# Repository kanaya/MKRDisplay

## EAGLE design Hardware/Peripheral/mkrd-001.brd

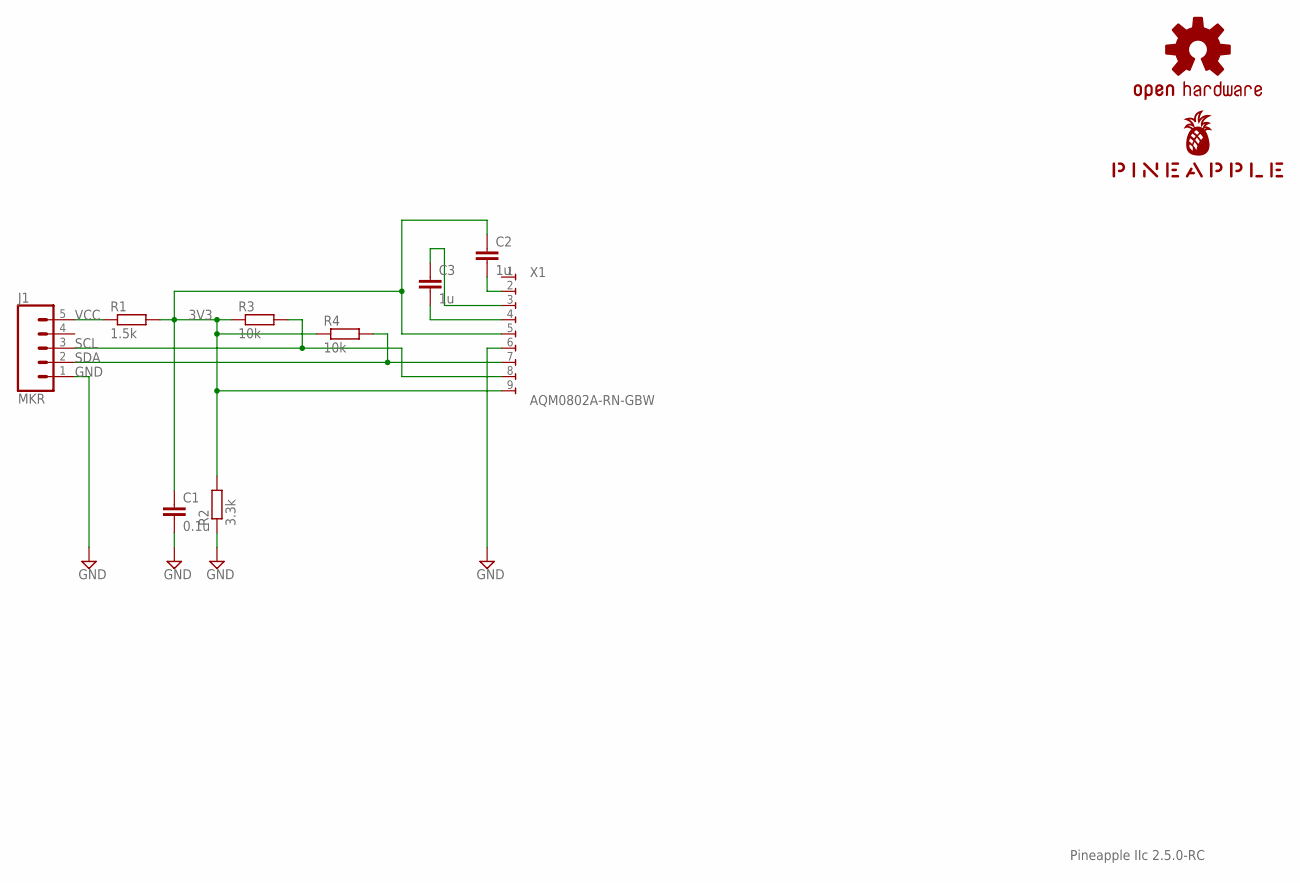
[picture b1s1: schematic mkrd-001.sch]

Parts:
C1: 0.1u; C025-024X044
C2, C3: 1u; C025-025X050
J1: MKR; JST-5-PTH
LOGO1: OSHW-LOGOS-COPPER; OSHW-LOGO-S_COPPER
R1: 1.5k; 0204/5
R2: 3.3k; 0204/5
R3, R4: 10k; 0204/5
U$1: PINEAPPLE450_SILK
X1: AQM0802A-RN-GBW; AQM0802A-RN-GBW-FOOTPRINT

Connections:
3V3: C1.1, C2.1, R1.2, R2.2, R3.1, R4.1, X1.5, X1.9
CAP1N: C3.1, X1.3
CAP1P: C3.2, X1.4
GND: C1.2, J1.1, R2.1, X1.6
LCDVOUT: C2.2, X1.2
SCL: J1.3, R3.2, X1.8
SDA: J1.2, R4.2, X1.7
VCC: J1.5, R1.1

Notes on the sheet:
Pineapple IIc 2.5.0-RC

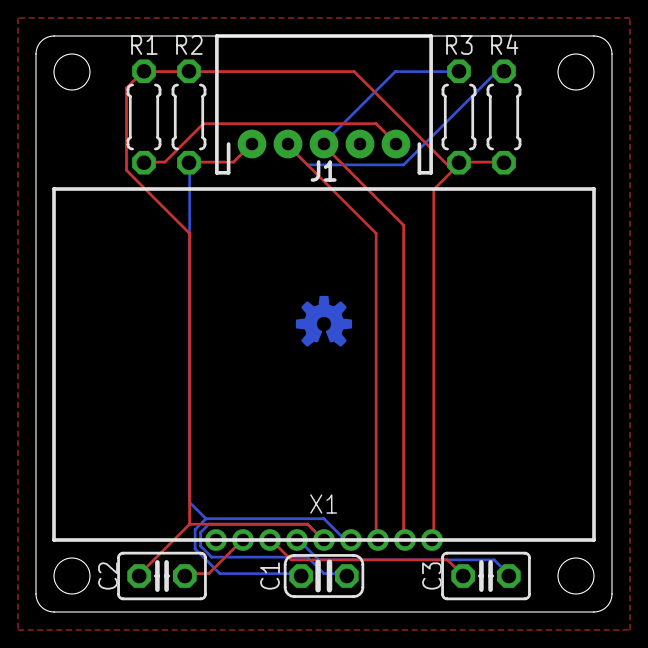
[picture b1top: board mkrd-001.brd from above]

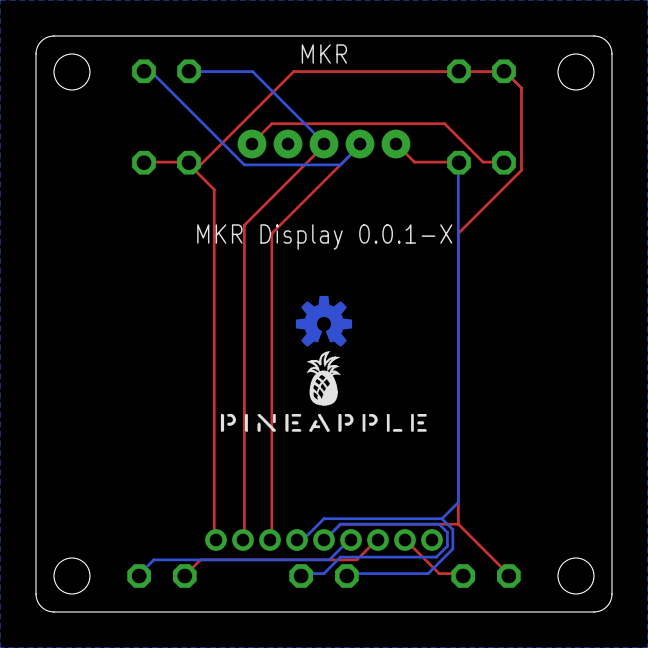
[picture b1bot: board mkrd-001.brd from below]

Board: 2 copper layers, 32.0 x 32.0 mm, 11 parts (2 on the bottom side), 8 nets.

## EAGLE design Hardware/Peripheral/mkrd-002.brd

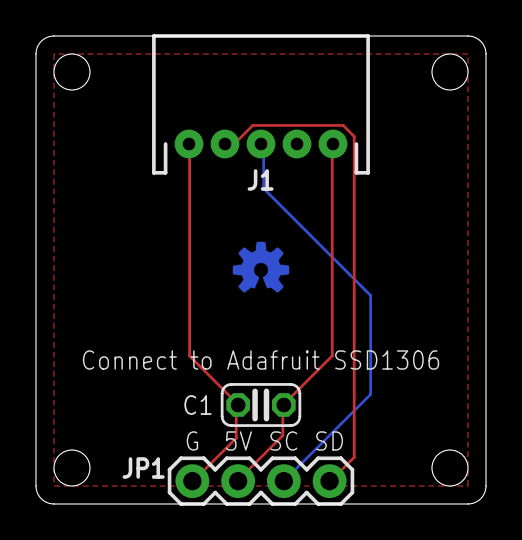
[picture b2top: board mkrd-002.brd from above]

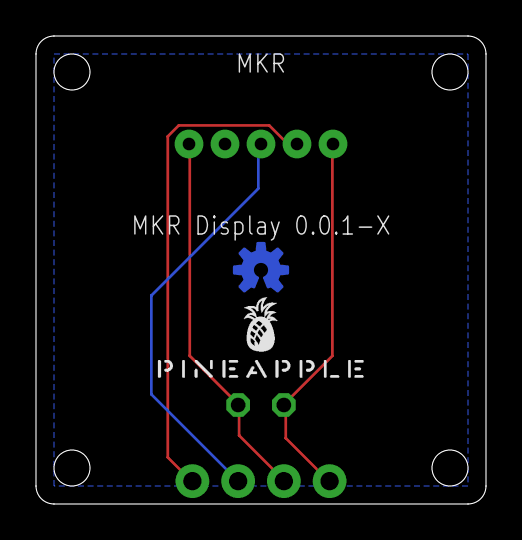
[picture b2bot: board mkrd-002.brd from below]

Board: 2 copper layers, 25.0 x 26.0 mm, 5 parts (2 on the bottom side), 4 nets.

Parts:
C1: C025-024X044
J1: MKR; JST-5-PTH
JP1: DISP; 1X04
LOGO1: OSHW-LOGOS-COPPER; OSHW-LOGO-S_COPPER
U$1: PINEAPPLE450_SILK

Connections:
GND: C1.2, J1.1, JP1.1
SCL: J1.3, JP1.3
SDA: J1.2, JP1.4
VCC: C1.1, J1.5, JP1.2

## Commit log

2022-02-19 Initial commit. Copied from Pineapple II Hex Sw.
2022-02-19 First try.
2022-02-20 Flipped MKR con.
2022-02-20 Added cap.
2022-02-21 Copy.
2022-02-22 Added new board.
2022-02-23 Signal name.
2022-02-23 GND pattern.
2022-02-23 Silk.

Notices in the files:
parts and their libraries:
SparkFun-Aesthetics: Licensing: Creative Commons ShareAlike 4.0 International - https://creativecommons.org/licenses/by-sa/4.0
